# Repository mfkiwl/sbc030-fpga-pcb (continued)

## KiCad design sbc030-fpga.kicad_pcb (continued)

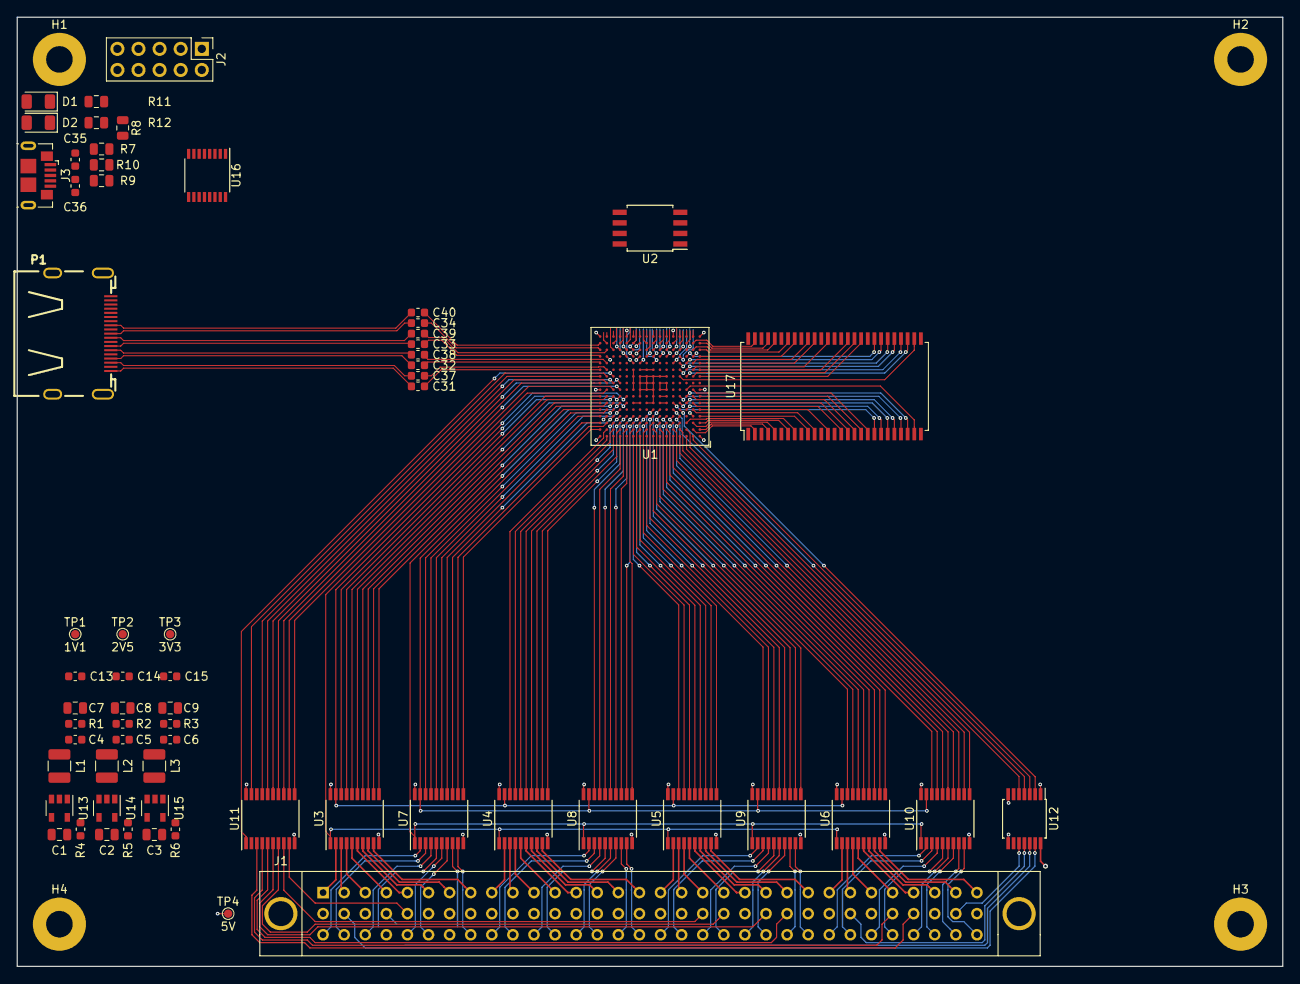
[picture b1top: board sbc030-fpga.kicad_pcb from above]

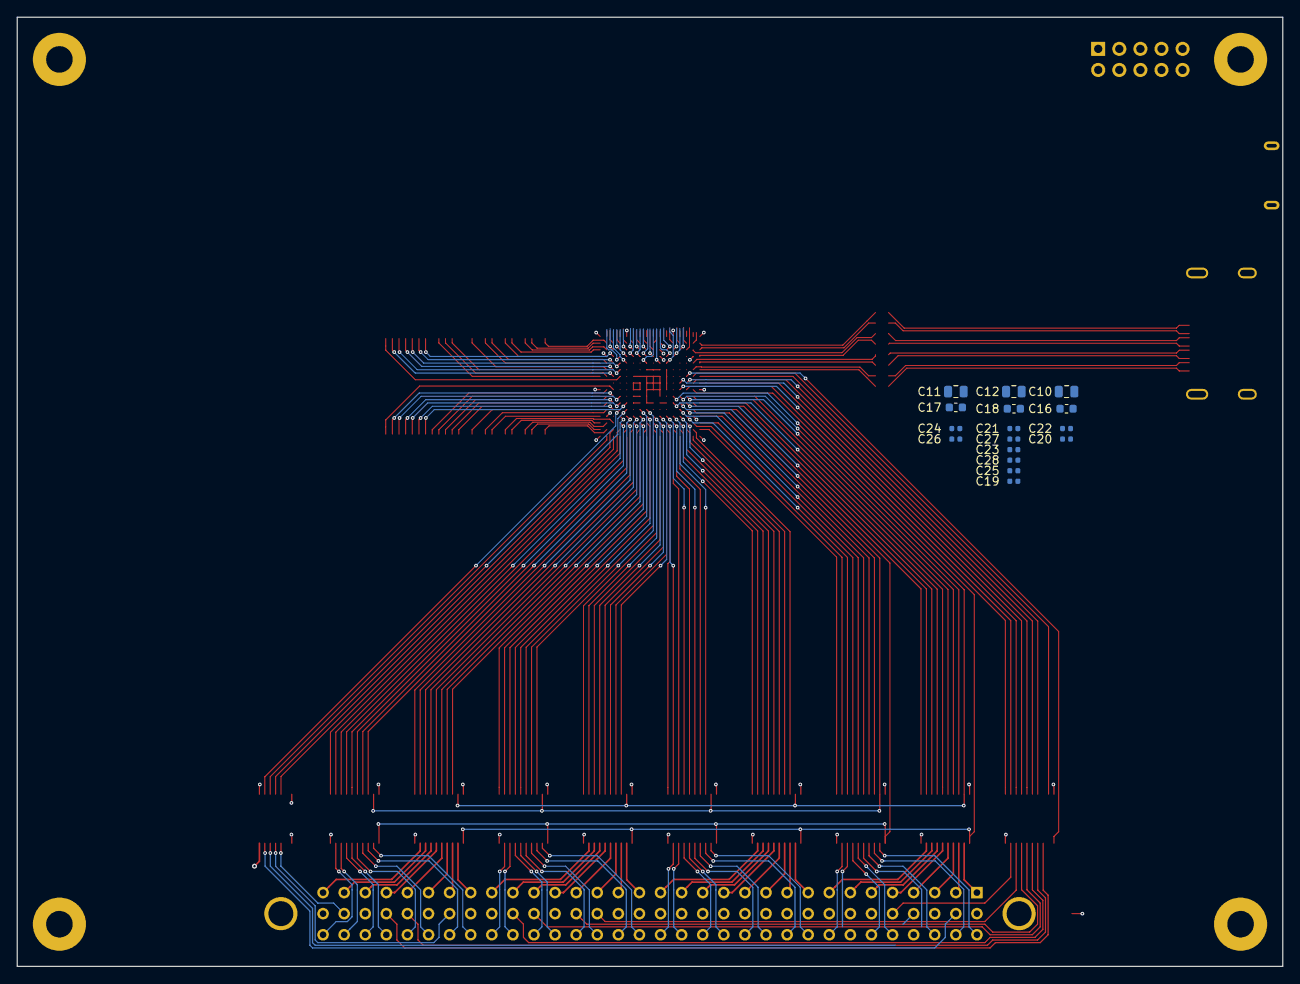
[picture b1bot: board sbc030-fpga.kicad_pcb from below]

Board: 4 copper layers, 152.4 x 114.3 mm, 84 parts (16 on the bottom side), 244 nets.

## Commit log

2018-12-30 use LFE5U-12F-8BG256C schematic symbol
2019-01-03 updated schematic and initial bga fanout
2019-01-04 fanout finished and starting work on level translators
2019-01-08 level translators done
2019-01-09 add sdram connections
2019-01-10 add hdmi library and missing footprint libraries
2019-01-11 add hdmi output
2019-01-11 small pin change in sdram
